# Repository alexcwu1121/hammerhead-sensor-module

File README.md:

# hammerhead-sensor-module

Electrical and software design files for the Hammerhead Sensor Module, top level control system of the Hammerhead mobile robot platform.

## 1. Software Development Prerequisites

Development for this project requires working within a devcontainer which has the Hammerhead Sensor Module Yocto SDK installed.

To build the Hammerhead Sensor Module Yocto image and SDK, you should have at least 50Gb of disk space.

For live remote gdb debugging and other niceties, make sure your board runs the development variant of the image, `hammerhead-dev-image`.

1. Note the version of the SDK required by the devcontainer config at `.devcontainer/devcontainer.json`. This is the version of the Hammerhead Yocto manifest which produces the SDK intended to be used with this revision of the Hammerhead Sensor Module software.
2. Pull down the specified tag of the Hammerhead Yocto manifest repo and follow BitBake environment setup instructions: https://github.com/alexcwu1121/yocto-hammerhead
3. Build the core Hammerhead image with SDK. This can take a few hours depending on your build hardware: `bitbake -c populate_sdk hammerhead-core-image`
4. Copy the SDK installer script at `~/build/tmp/deploy/sdk/hammerhead-glibc-x86_64-hammerhead-core-image-cortexa76-hammerhead-toolchain-<version>.sh` to the root of this repo
5. Install Podman >4.x
6. Install VSCode
7. Install VSCode Dev Containers extension
8. In Dev Containers settings, set the following:
    - Docker Path: `podman`
    - Docker Compose Path: `podman-compose`
    - Docker Socket: `/run/podman/podman.sock`
9. Open VSCode to this directory and select from command pallette `Dev Containers: Rebuild and Reopen in Container`
10. VSCode will build the devcontainer, including copying in and installing the SDK. This may take several minutes.

## 2. Deploying and Debugging on Target

The target is expected at `192.168.4.1` (the board's access point gateway), logged in as `root`. Both can be changed in `.vscode/settings.json` (`hammerhead.targetHost`, `hammerhead.targetUser`, `hammerhead.gdbPort`), or with the `HAMMERHEAD_HOST`/`HAMMERHEAD_USER` environment variables when running the scripts directly.

### Target Password

The password is never stored. The first deploy or debug session of a devcontainer session prompts for it in the task terminal, then keeps an SSH master connection open in the background; later deploys and debug sessions reuse it without prompting. The connection closes when the devcontainer stops or the board drops off the network, after which the next run prompts again. To close it manually (e.g. after reflashing or to switch boards), run `Tasks: Run Task` -> `Target: disconnect`.

### Deploy

From the command palette, `Tasks: Run Task` -> `Deploy: diagnostics`. This builds the `Target-Debug` preset and copies `hsc-diagnostics` to `/opt/diagnostics/` on the target.

Or from a devcontainer terminal:

```
./scripts/deploy.sh build/Target-Debug/cpp/diagnostics/hsc-diagnostics /opt/diagnostics
```

### Remote Debug

From the command palette, `Debug: Select and Start Debugging` -> `Remote Debug: diagnostics` (or `F5`). This builds, deploys, starts `gdbserver` on the target, and attaches the SDK's cross gdb. The application's stdout/stderr appears in the `GDB Server: diagnostics` terminal.

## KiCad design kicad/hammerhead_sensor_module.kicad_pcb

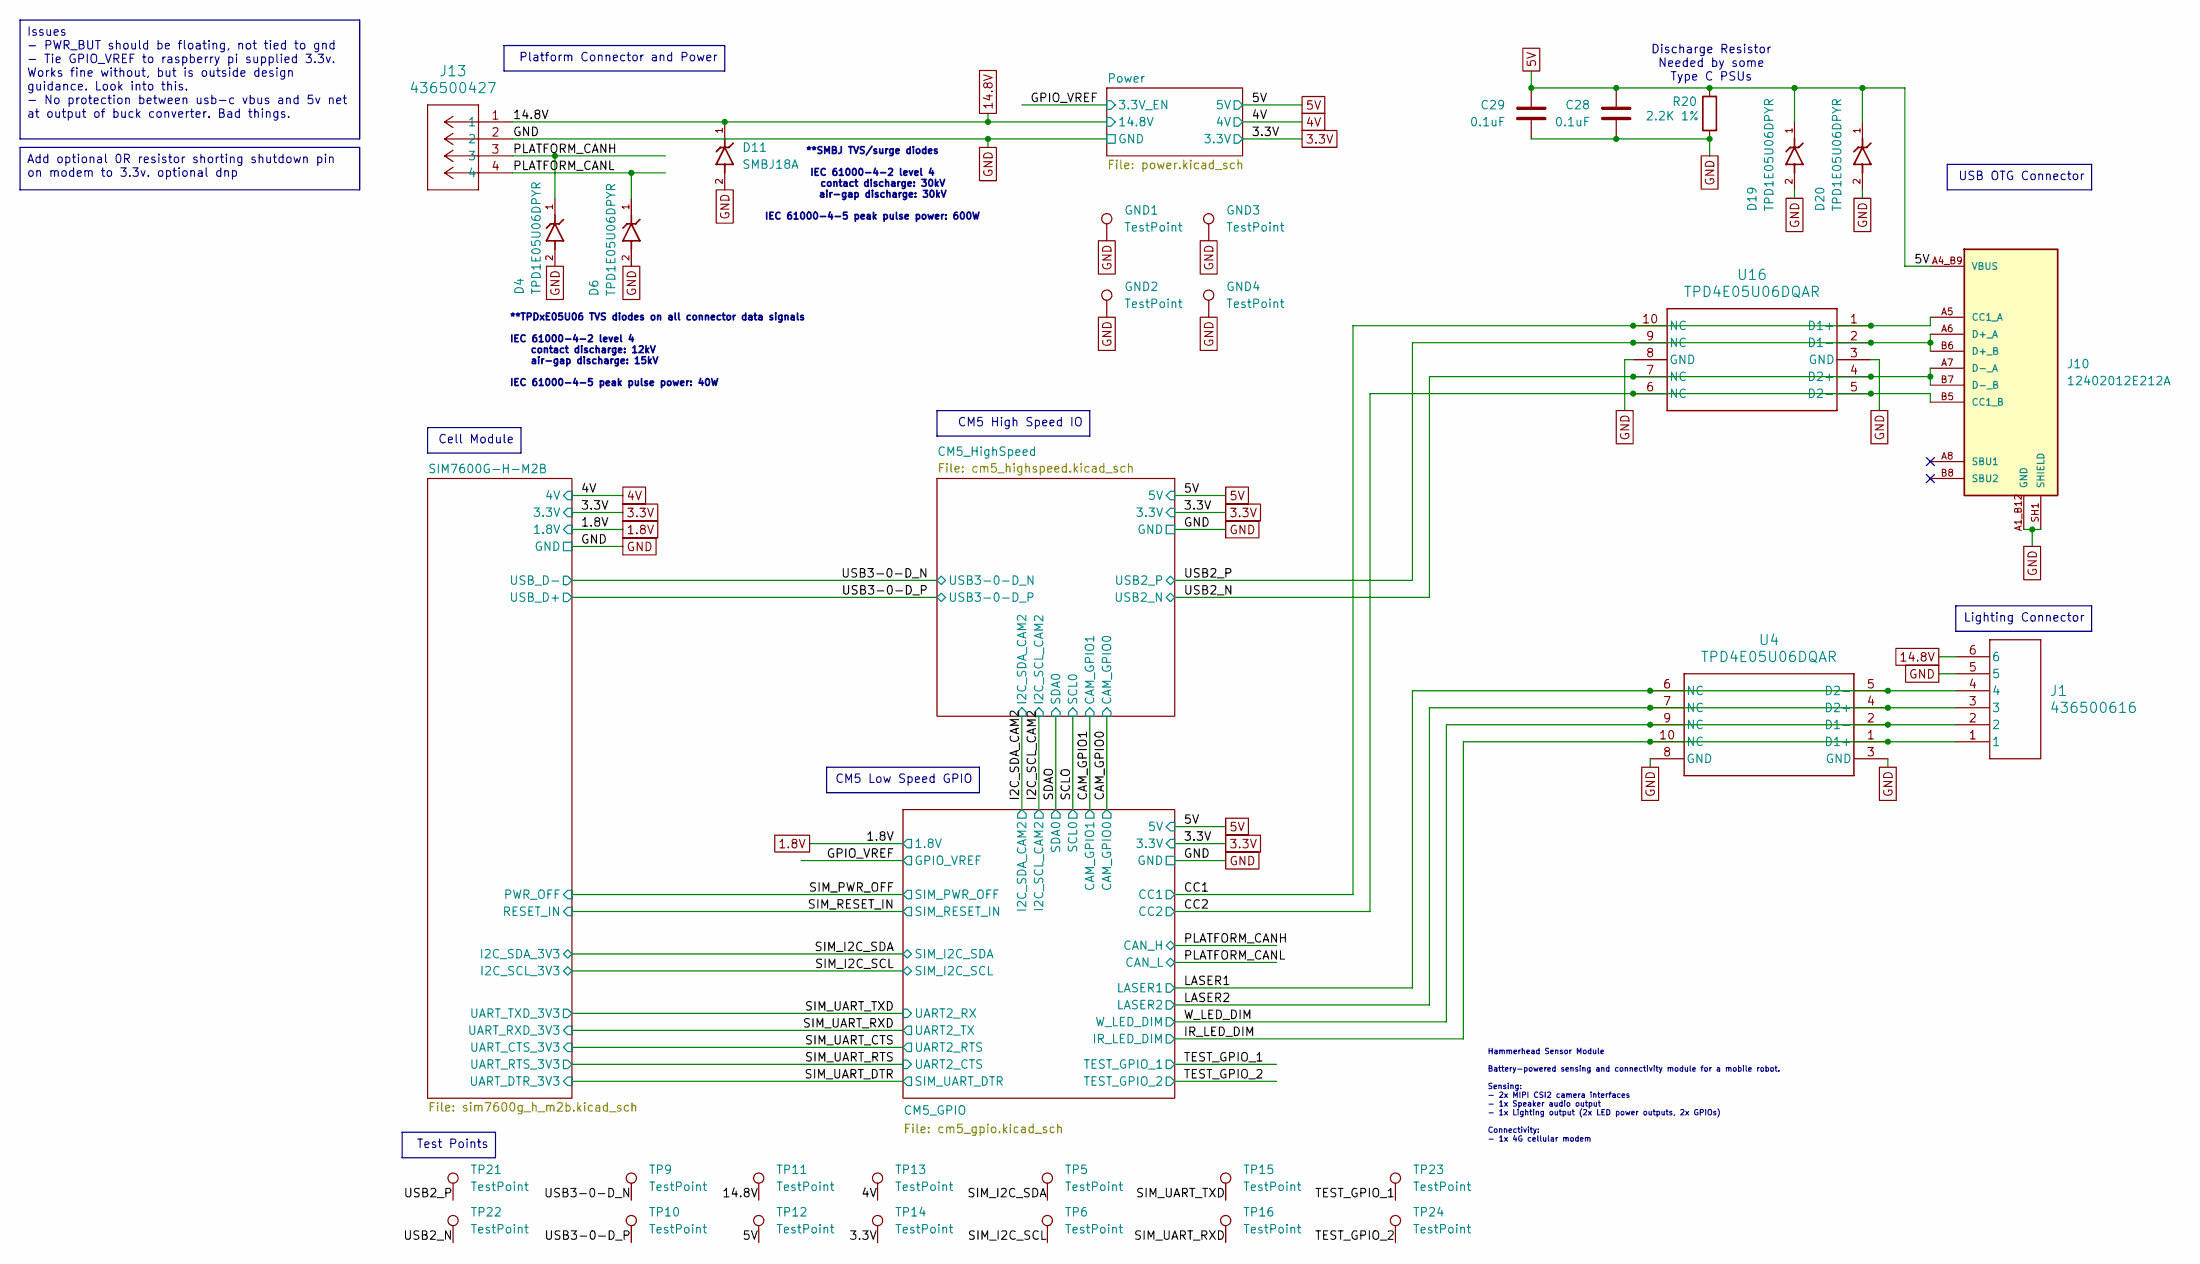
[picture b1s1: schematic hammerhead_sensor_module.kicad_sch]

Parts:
C28, C29: 0.1uF; C_0201_0603Metric
D4, D6, D19, D20: TPD1E05U06DPYR; SON65P60X100X45-2N
D11: SMBJ18A; DIOM5436X261N; PARTREV JC.07/04/25 v4
GND1, GND2, GND3, GND4: TestPoint; TestPoint_Pad_1.0x1.0mm
J1: 436500616; CONN_SD-43650-006_06_MOL
J10: 12402012E212A; AMPHENOL_12402012E212A; PARTREV 4
J13: 436500427; CONN_SD-43650-010_04_MOL
R20: 2.2K 1%; R_0201_0603Metric; Part Description Resistor 2.2K M1005 1% 63mW
TP5, TP6, TP9, TP10, TP11, TP12, TP13, TP14, TP15, TP16, TP21, TP22, TP23, TP24: TestPoint; TestPoint_Pad_1.0x1.0mm
U4, U16: TPD4E05U06DQAR; DQA0010A

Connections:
3.3V: TP14.1; also elsewhere on the board
4V: TP13.1; also elsewhere on the board
5V: C28.1, C29.1, D19.1, D20.1, J10.A4_B9 (VBUS), J10.B4_A9 (VBUS), R20.1, TP12.1; also elsewhere on the board
14.8V: D11.1, J1.6, J13.1, TP11.1; also elsewhere on the board
/CC1: J10.A5 (CC1_A), U16.1 (D1+), U16.10 (NC); also elsewhere on the board
/CC2: J10.B5 (CC1_B), U16.5 (D2-), U16.6 (NC); also elsewhere on the board
/IR_LED_DIM: J1.1, U4.1 (D1+), U4.10 (NC); also elsewhere on the board
/LASER1: J1.4, U4.5 (D2-), U4.6 (NC); also elsewhere on the board
/LASER2: J1.3, U4.4 (D2+), U4.7 (NC); also elsewhere on the board
/PLATFORM_CANH: D4.1, J13.3; also elsewhere on the board
/PLATFORM_CANL: D6.1, J13.4; also elsewhere on the board
/SIM_I2C_SCL: TP6.1; also elsewhere on the board
/SIM_I2C_SDA: TP5.1; also elsewhere on the board
/SIM_UART_RXD: TP16.1; also elsewhere on the board
/SIM_UART_TXD: TP15.1; also elsewhere on the board
/TEST_GPIO_1: TP23.1; also elsewhere on the board
/TEST_GPIO_2: TP24.1; also elsewhere on the board
/USB2_N: J10.A7 (D-_A), J10.B7 (D-_B), TP22.1, U16.4 (D2+), U16.7 (NC); also elsewhere on the board
/USB2_P: J10.A6 (D+_A), J10.B6 (D+_B), TP21.1, U16.2 (D1-), U16.9 (NC); also elsewhere on the board
/USB3-0-D_N: TP9.1; also elsewhere on the board
/USB3-0-D_P: TP10.1; also elsewhere on the board
/W_LED_DIM: J1.2, U4.2 (D1-), U4.9 (NC); also elsewhere on the board
GND: C28.2, C29.2, D4.2, D6.2, D11.2, D19.2, D20.2, GND1.1, GND2.1, GND3.1, GND4.1, J1.5, J10.A1_B12 (GND), J10.B1_A12 (GND), J10.SH1 (SHIELD), J10.SH2 (SHIELD), J10.SH3 (SHIELD), J10.SH4 (SHIELD), J13.2, R20.2, U4.3 (GND), U4.8 (GND), U16.3 (GND), U16.8 (GND); also elsewhere on the board

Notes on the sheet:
Hammerhead Sensor Module Battery-powered sensing and connectivity module for a mobile robot. Sensing: - 2x MIPI CSI2 camera interfaces - 1x Speaker audio output - 1x Lighting output (2x LED power outputs, 2x GPIOs) Connectivity: - 1x 4G cellular modem
**SMBJ TVS/surge diodes IEC 61000-4-2 level 4 contact discharge: 30kV air-gap discharge: 30kV IEC 61000-4-5 peak pulse power: 600W
**TPDxE05U06 TVS diodes on all connector data signals IEC 61000-4-2 level 4 contact discharge: 12kV air-gap discharge: 15kV IEC 61000-4-5 peak pulse power: 40W
Discharge Resistor Needed by some Type C PSUs
Cell Module
Test Points
Issues - PWR_BUT should be floating, not tied to gnd - Tie GPIO_VREF to raspberry pi supplied 3.3v. Works fine without, but is outside design guidance. Look into this. - No protection between usb-c vbus and 5v net at output of buck converter. Bad things.
Add optional 0R resistor shorting shutdown pin on modem to 3.3v. optional dnp
USB OTG Connector
CM5 High Speed IO
Platform Connector and Power
Lighting Connector
CM5 Low Speed GPIO

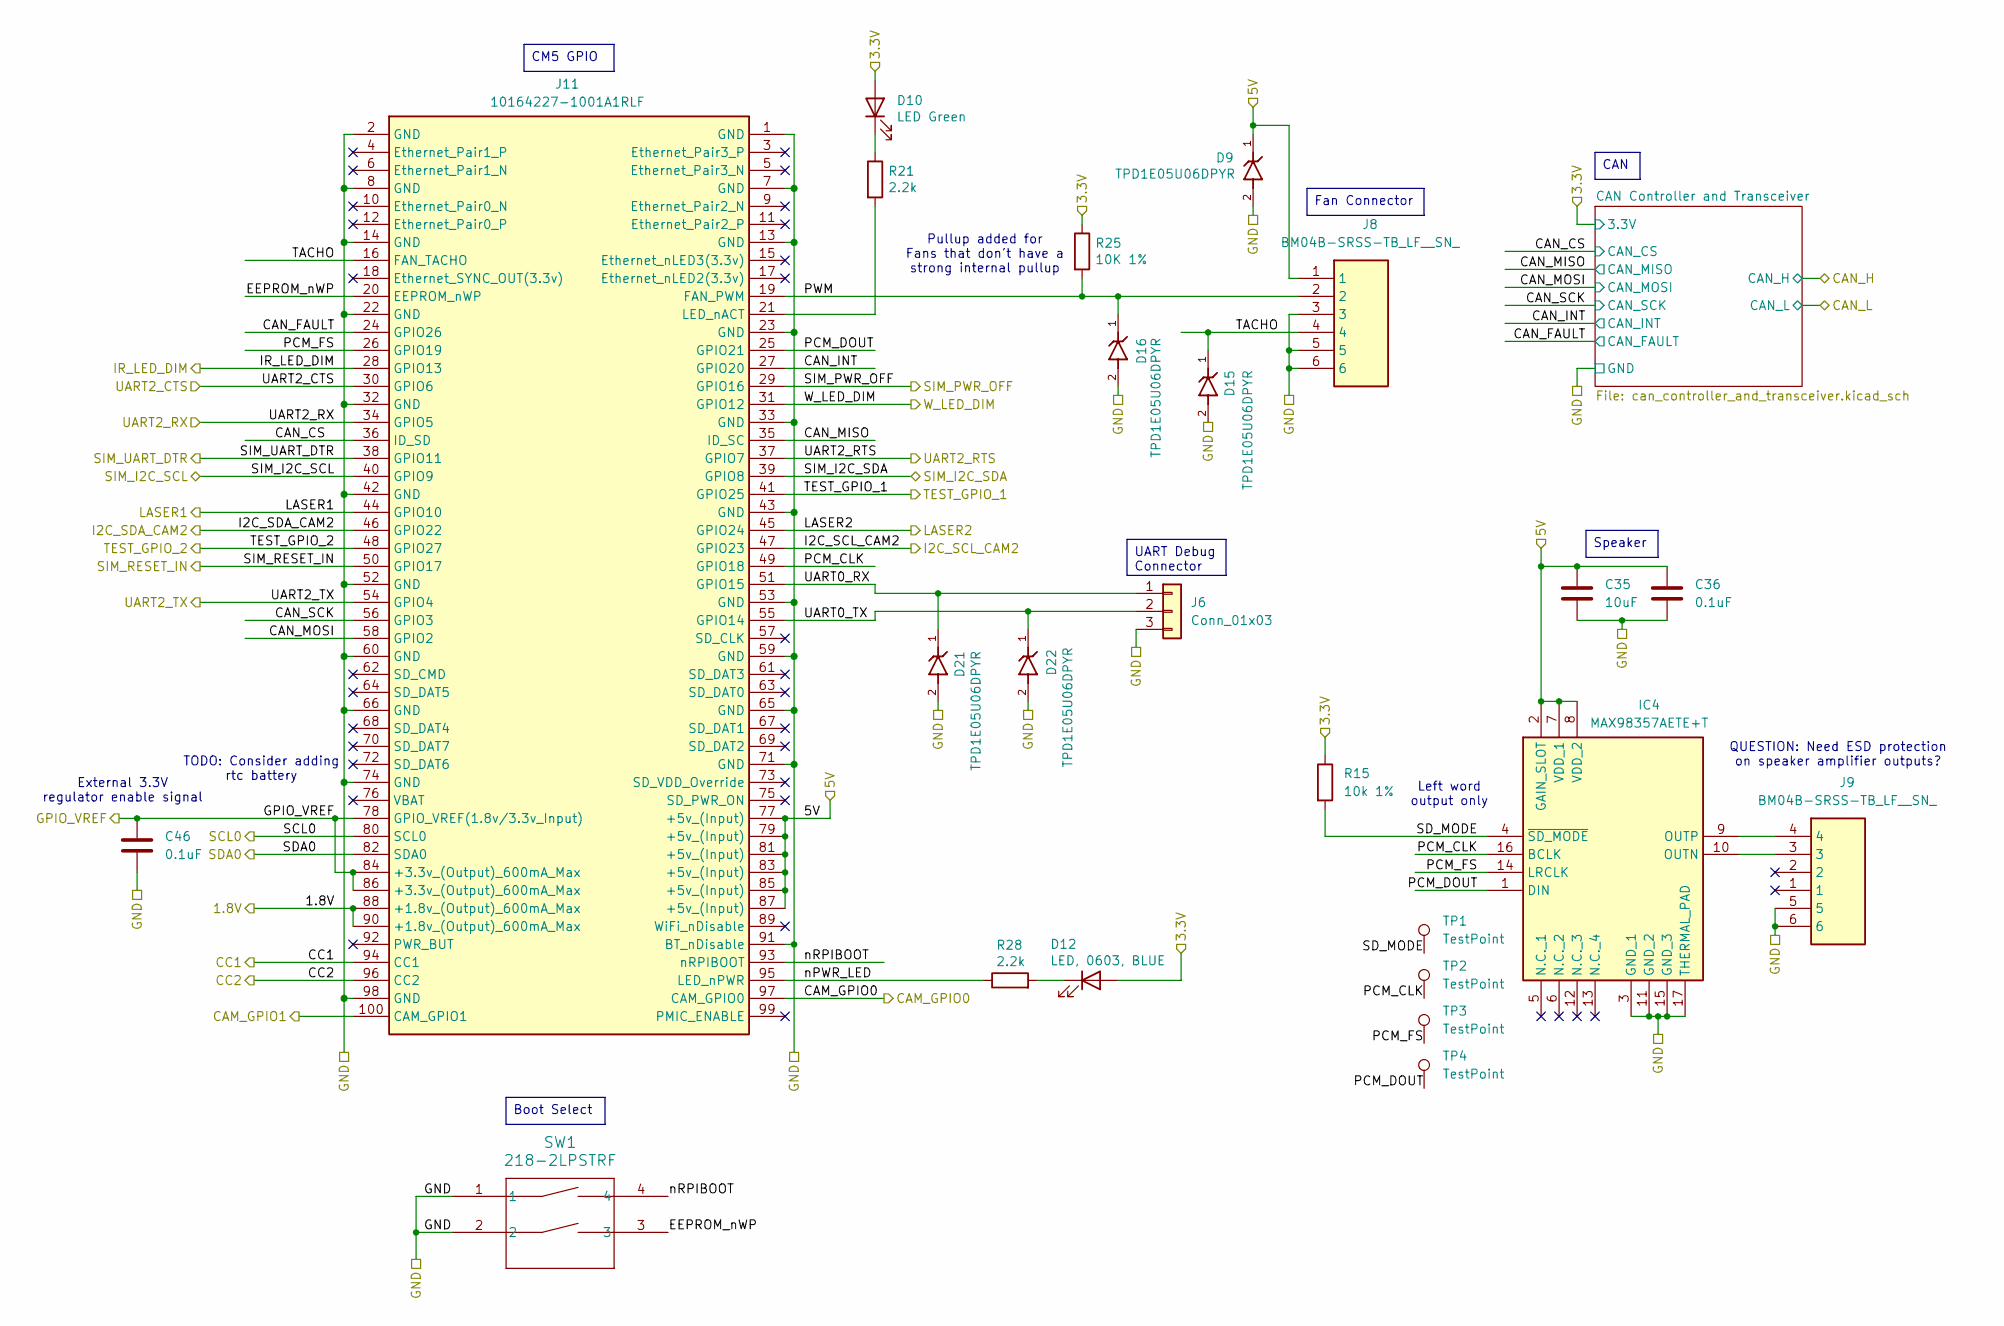
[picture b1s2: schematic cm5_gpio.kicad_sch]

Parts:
C35: 10uF; C_0603_1608Metric
C36, C46: 0.1uF; C_0201_0603Metric
D9, D15, D16, D21, D22: TPD1E05U06DPYR; SON65P60X100X45-2N
D10: LED Green; LED_0603_1608Metric; Part Description Green 572nm LED Indication - Discrete 2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
D12: LED, 0603, BLUE; LED_0603_1608Metric; Part Description Red 620nm LED Indication - Discrete 2.2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
IC4: MAX98357AETE+T; QFN50P300X300X80-17N; Manufacturer_Part_Number MAX98357AETE+T; Mouser Part Number 700-MAX98357AETE+T
J6: Conn_01x03; PinHeader_1x03_P2.54mm_Vertical
J8, J9: BM04B-SRSS-TB_LF__SN_; BM04B-SRSS-TB_LFSN_; Manufacturer_Part_Number BM04B-SRSS-TB(LF)(SN); Mouser Part Number N/A
J11: 10164227-1001A1RLF; 101642271001A1RLF; Manufacturer_Part_Number 10164227-1001A1RLF; Mouser Part Number 649-01642271001A1RLF
R15: 10k 1%; R_0201_0603Metric
R21, R28: 2.2k; R_0201_0603Metric; Part Description Resistor 1K M1005 1% 63mW
R25: 10K 1%; R_0201_0603Metric; Part Description Resistor 10K M1005 1% 63mW
SW1: 218-2LPSTRF; 218-2-GULLWING_CTS
TP1, TP2, TP3, TP4: TestPoint; TestPoint_Pad_1.0x1.0mm

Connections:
1.8V: J11.88 (+1.8v_(Output)_600mA_Max), J11.90 (+1.8v_(Output)_600mA_Max); also elsewhere on the board
3.3V: D10.2 (A), D12.2 (A), R15.1, R25.1; also elsewhere on the board
5V: C35.1, C36.1, D9.1, IC4.2 (GAIN_SLOT), IC4.7 (VDD_1), IC4.8 (VDD_2), J8.1, J11.77 (+5v_(Input)), J11.79 (+5v_(Input)), J11.81 (+5v_(Input)), J11.83 (+5v_(Input)), J11.85 (+5v_(Input)), J11.87 (+5v_(Input)); also elsewhere on the board
/CAM_GPIO0: J11.97 (CAM_GPIO0); also elsewhere on the board
/CAM_GPIO1: J11.100 (CAM_GPIO1); also elsewhere on the board
/CC1: J11.94 (CC1); also elsewhere on the board
/CC2: J11.96 (CC2); also elsewhere on the board
/CM5_GPIO/CAN_CS: J11.36 (ID_SD); also elsewhere on the board
/CM5_GPIO/CAN_FAULT: J11.24 (GPIO26); also elsewhere on the board
/CM5_GPIO/CAN_INT: J11.27 (GPIO20); also elsewhere on the board
/CM5_GPIO/CAN_MISO: J11.35 (ID_SC); also elsewhere on the board
/CM5_GPIO/CAN_MOSI: J11.58 (GPIO2); also elsewhere on the board
/CM5_GPIO/CAN_SCK: J11.56 (GPIO3); also elsewhere on the board
/CM5_GPIO/EEPROM_nWP: J11.20 (EEPROM_nWP), SW1.3
/CM5_GPIO/PCM_CLK: IC4.16 (BCLK), J11.49 (GPIO18), TP2.1
/CM5_GPIO/PCM_DOUT: IC4.1 (DIN), J11.25 (GPIO21), TP4.1
/CM5_GPIO/PCM_FS: IC4.14 (LRCLK), J11.26 (GPIO19), TP3.1
/CM5_GPIO/PWM: D16.1, J8.2, J11.19 (FAN_PWM), R25.2
/CM5_GPIO/SD_MODE: IC4.4 (~SD_MODE), R15.2, TP1.1
/CM5_GPIO/TACHO: D15.1, J8.4, J11.16 (FAN_TACHO)
/CM5_GPIO/UART0_RX: D21.1, J6.1, J11.51 (GPIO15)
/CM5_GPIO/UART0_TX: D22.1, J6.2, J11.55 (GPIO14)
/CM5_GPIO/nPWR_LED: J11.95 (LED_nPWR), R28.1
/CM5_GPIO/nRPIBOOT: J11.93 (nRPIBOOT), SW1.4
/GPIO_VREF: C46.1, J11.78 (GPIO_VREF(1.8v/3.3v_Input)), J11.84 (+3.3v_(Output)_600mA_Max), J11.86 (+3.3v_(Output)_600mA_Max); also elsewhere on the board
/I2C_SCL_CAM2: J11.47 (GPIO23); also elsewhere on the board
/I2C_SDA_CAM2: J11.46 (GPIO22); also elsewhere on the board
/IR_LED_DIM: J11.28 (GPIO13); also elsewhere on the board
/LASER1: J11.44 (GPIO10); also elsewhere on the board
/LASER2: J11.45 (GPIO24); also elsewhere on the board
/SCLO: J11.80 (SCL0); also elsewhere on the board
/SDAO: J11.82 (SDA0); also elsewhere on the board
/SIM_I2C_SCL: J11.40 (GPIO9); also elsewhere on the board
/SIM_I2C_SDA: J11.39 (GPIO8); also elsewhere on the board
/SIM_PWR_OFF: J11.29 (GPIO16); also elsewhere on the board
/SIM_RESET_IN: J11.50 (GPIO17); also elsewhere on the board
/SIM_UART_CTS: J11.37 (GPIO7); also elsewhere on the board
/SIM_UART_DTR: J11.38 (GPIO11); also elsewhere on the board
/SIM_UART_RTS: J11.30 (GPIO6); also elsewhere on the board
/SIM_UART_RXD: J11.54 (GPIO4); also elsewhere on the board
/SIM_UART_TXD: J11.34 (GPIO5); also elsewhere on the board
/TEST_GPIO_1: J11.41 (GPIO25); also elsewhere on the board
/TEST_GPIO_2: J11.48 (GPIO27); also elsewhere on the board
/W_LED_DIM: J11.31 (GPIO12); also elsewhere on the board
GND: C35.2, C36.2, C46.2, D9.2, D15.2, D16.2, D21.2, D22.2, IC4.3 (GND_1), IC4.11 (GND_2), IC4.15 (GND_3), IC4.17 (THERMAL_PAD), J6.3, J8.3, J8.5, J8.6, J9.5, J9.6, J11.1 (GND), J11.2 (GND), J11.7 (GND), J11.8 (GND), J11.13 (GND), J11.14 (GND), J11.22 (GND), J11.23 (GND), J11.32 (GND), J11.33 (GND), J11.42 (GND), J11.43 (GND), J11.52 (GND), J11.53 (GND), J11.59 (GND), J11.60 (GND), J11.65 (GND), J11.66 (GND), J11.71 (GND), J11.74 (GND), J11.91 (BT_nDisable), J11.98 (GND), SW1.1, SW1.2; also elsewhere on the board
unnamed: D10.1 (K), R21.1
unnamed: D12.1 (K), R28.2
unnamed: IC4.10 (OUTN), J9.3
unnamed: IC4.9 (OUTP), J9.4
unnamed: J11.21 (LED_nACT), R21.2

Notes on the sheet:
External 3.3V regulator enable signal
TODO: Consider adding rtc battery
Pullup added for Fans that don't have a strong internal pullup
QUESTION: Need ESD protection on speaker amplifier outputs?
Left word output only
UART Debug Connector
CM5 GPIO
Speaker
Boot Select
Fan Connector
CAN

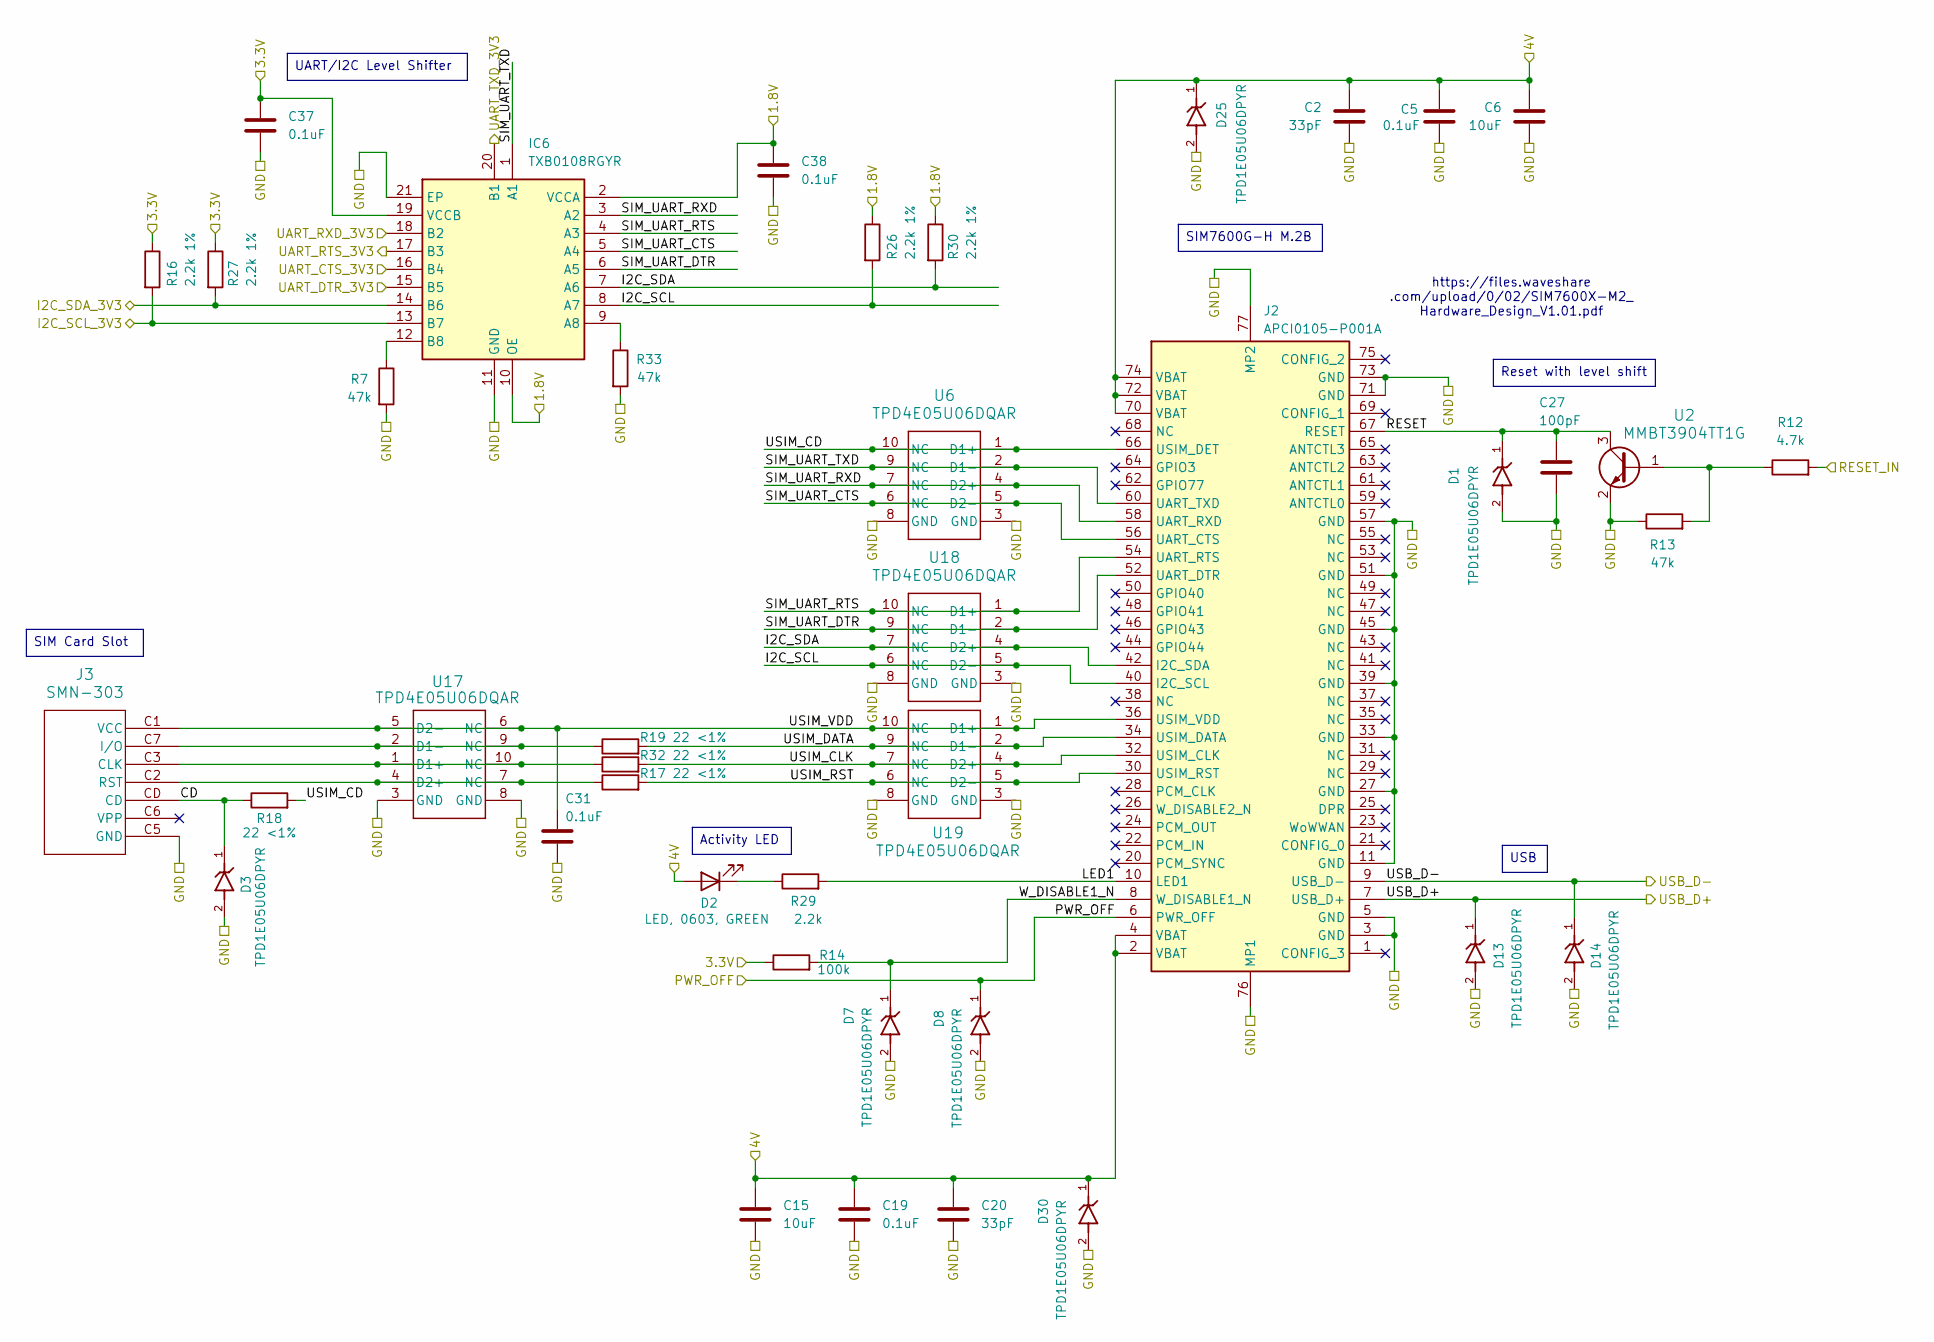
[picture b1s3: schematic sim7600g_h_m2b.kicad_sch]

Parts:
C2, C20: 33pF; C_0402_1005Metric
C5, C19: 0.1uF; C_0402_1005Metric
C6, C15: 10uF; C_0603_1608Metric
C27: 100pF; C_0201_0603Metric
C31, C37, C38: 0.1uF; C_0201_0603Metric
D1, D3, D7, D8, D13, D14, D25, D30: TPD1E05U06DPYR; SON65P60X100X45-2N
D2: LED, 0603, GREEN; D_0603_1608Metric
IC6: TXB0108RGYR; SN74LVC541ARGYR; Manufacturer_Part_Number TXB0108RGYR; Mouser Part Number 595-TXB0108RGYR
J2: APCI0105-P001A; APCI0105P001A; Manufacturer_Part_Number APCI0105-P001A
J3: SMN-303; SMN-303_XNP
R7, R13, R33: 47k; R_0201_0603Metric
R12: 4.7k; R_0201_0603Metric
R14: 100k; R_0201_0603Metric
R16, R26, R27, R30: 2.2k 1%; R_0201_0603Metric
R17, R18, R19, R32: 22 <1%; R_0201_0603Metric
R29: 2.2k; R_0201_0603Metric
U2: MMBT3904TT1G; SOT-416_1P65X0P9_ONS-L
U6, U17, U18, U19: TPD4E05U06DQAR; DQA0010A

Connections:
1.8V: C38.1, IC6.2 (VCCA), IC6.10 (OE), R26.1, R30.1; also elsewhere on the board
3.3V: C37.1, IC6.19 (VCCB), R14.1, R16.1, R27.1; also elsewhere on the board
4V: C2.1, C5.1, C6.1, C15.1, C19.1, C20.1, D2.2 (A), D25.1, D30.1, J2.2 (VBAT), J2.4 (VBAT), J2.70 (VBAT), J2.72 (VBAT), J2.74 (VBAT); also elsewhere on the board
/SIM7600G-H-M2B/CD: D3.1, J3.CD, R18.1
/SIM7600G-H-M2B/I2C_SCL: IC6.8 (A7), J2.40 (I2C_SCL), R26.2, U18.5 (D2-), U18.6 (NC)
/SIM7600G-H-M2B/I2C_SDA: IC6.7 (A6), J2.42 (I2C_SDA), R30.2, U18.4 (D2+), U18.7 (NC)
/SIM7600G-H-M2B/LED1: J2.10 (LED1), R29.2
/SIM7600G-H-M2B/RESET: C27.1, D1.1, J2.67 (RESET), U2.3
/SIM7600G-H-M2B/SIM_UART_CTS: IC6.5 (A4), J2.56 (UART_CTS), U6.5 (D2-), U6.6 (NC)
/SIM7600G-H-M2B/SIM_UART_DTR: IC6.6 (A5), J2.52 (UART_DTR), U18.2 (D1-), U18.9 (NC)
/SIM7600G-H-M2B/SIM_UART_RTS: IC6.4 (A3), J2.54 (UART_RTS), U18.1 (D1+), U18.10 (NC)
/SIM7600G-H-M2B/SIM_UART_RXD: IC6.3 (A2), J2.58 (UART_RXD), U6.4 (D2+), U6.7 (NC)
/SIM7600G-H-M2B/SIM_UART_TXD: IC6.1 (A1), J2.60 (UART_TXD), U6.2 (D1-), U6.9 (NC)
/SIM7600G-H-M2B/USIM_CD: J2.66 (USIM_DET), R18.2, U6.1 (D1+), U6.10 (NC)
/SIM7600G-H-M2B/USIM_CLK: J2.32 (USIM_CLK), R32.2, U19.4 (D2+), U19.7 (NC)
/SIM7600G-H-M2B/USIM_DATA: J2.34 (USIM_DATA), R19.2, U19.2 (D1-), U19.9 (NC)
/SIM7600G-H-M2B/USIM_RST: J2.30 (USIM_RST), R17.2, U19.5 (D2-), U19.6 (NC)
/SIM7600G-H-M2B/USIM_VDD: C31.1, J2.36 (USIM_VDD), J3.C1 (VCC), U17.5 (D2-), U17.6 (NC), U19.1 (D1+), U19.10 (NC)
/SIM7600G-H-M2B/W_DISABLE1_N: D7.1, J2.8 (W_DISABLE1_N), R14.2
/SIM_I2C_SCL: IC6.13 (B7), R16.2; also elsewhere on the board
/SIM_I2C_SDA: IC6.14 (B6), R27.2; also elsewhere on the board
/SIM_PWR_OFF: D8.1, J2.6 (PWR_OFF); also elsewhere on the board
/SIM_RESET_IN: R12.2; also elsewhere on the board
/SIM_UART_CTS: IC6.16 (B4); also elsewhere on the board
/SIM_UART_DTR: IC6.15 (B5); also elsewhere on the board
/SIM_UART_RTS: IC6.17 (B3); also elsewhere on the board
/SIM_UART_RXD: IC6.18 (B2); also elsewhere on the board
/SIM_UART_TXD: IC6.20 (B1); also elsewhere on the board
/USB3-0-D_N: D14.1, J2.9 (USB_D-); also elsewhere on the board
/USB3-0-D_P: D13.1, J2.7 (USB_D+); also elsewhere on the board
GND: C2.2, C5.2, C6.2, C15.2, C19.2, C20.2, C27.2, C31.2, C37.2, C38.2, D1.2, D3.2, D7.2, D8.2, D13.2, D14.2, D25.2, D30.2, IC6.11 (GND), IC6.21 (EP), J2.3 (GND), J2.5 (GND), J2.11 (GND), J2.27 (GND), J2.33 (GND), J2.39 (GND), J2.45 (GND), J2.51 (GND), J2.57 (GND), J2.71 (GND), J2.73 (GND), J2.76 (MP1), J2.77 (MP2), J3.C5 (GND), R7.2, R13.1, R33.2, U2.2, U6.3 (GND), U6.8 (GND), U17.3 (GND), U17.8 (GND), U18.3 (GND), U18.8 (GND), U19.3 (GND), U19.8 (GND); also elsewhere on the board
unnamed: D2.1 (K), R29.1
unnamed: IC6.9 (A8), R33.1
unnamed: IC6.12 (B8), R7.1
unnamed: J3.C3 (CLK), R32.1, U17.1 (D1+), U17.10 (NC)
unnamed: J3.C7 (I/O), R19.1, U17.2 (D1-), U17.9 (NC)
unnamed: J3.C2 (RST), R17.1, U17.4 (D2+), U17.7 (NC)
unnamed: R12.1, R13.2, U2.1

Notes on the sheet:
https://files.waveshare .com/upload/0/02/SIM7600X-M2_ Hardware_Design_V1.01.pdf
USB
Reset with level shift
SIM Card Slot
SIM7600G-H M.2B
Activity LED
UART/I2C Level Shifter

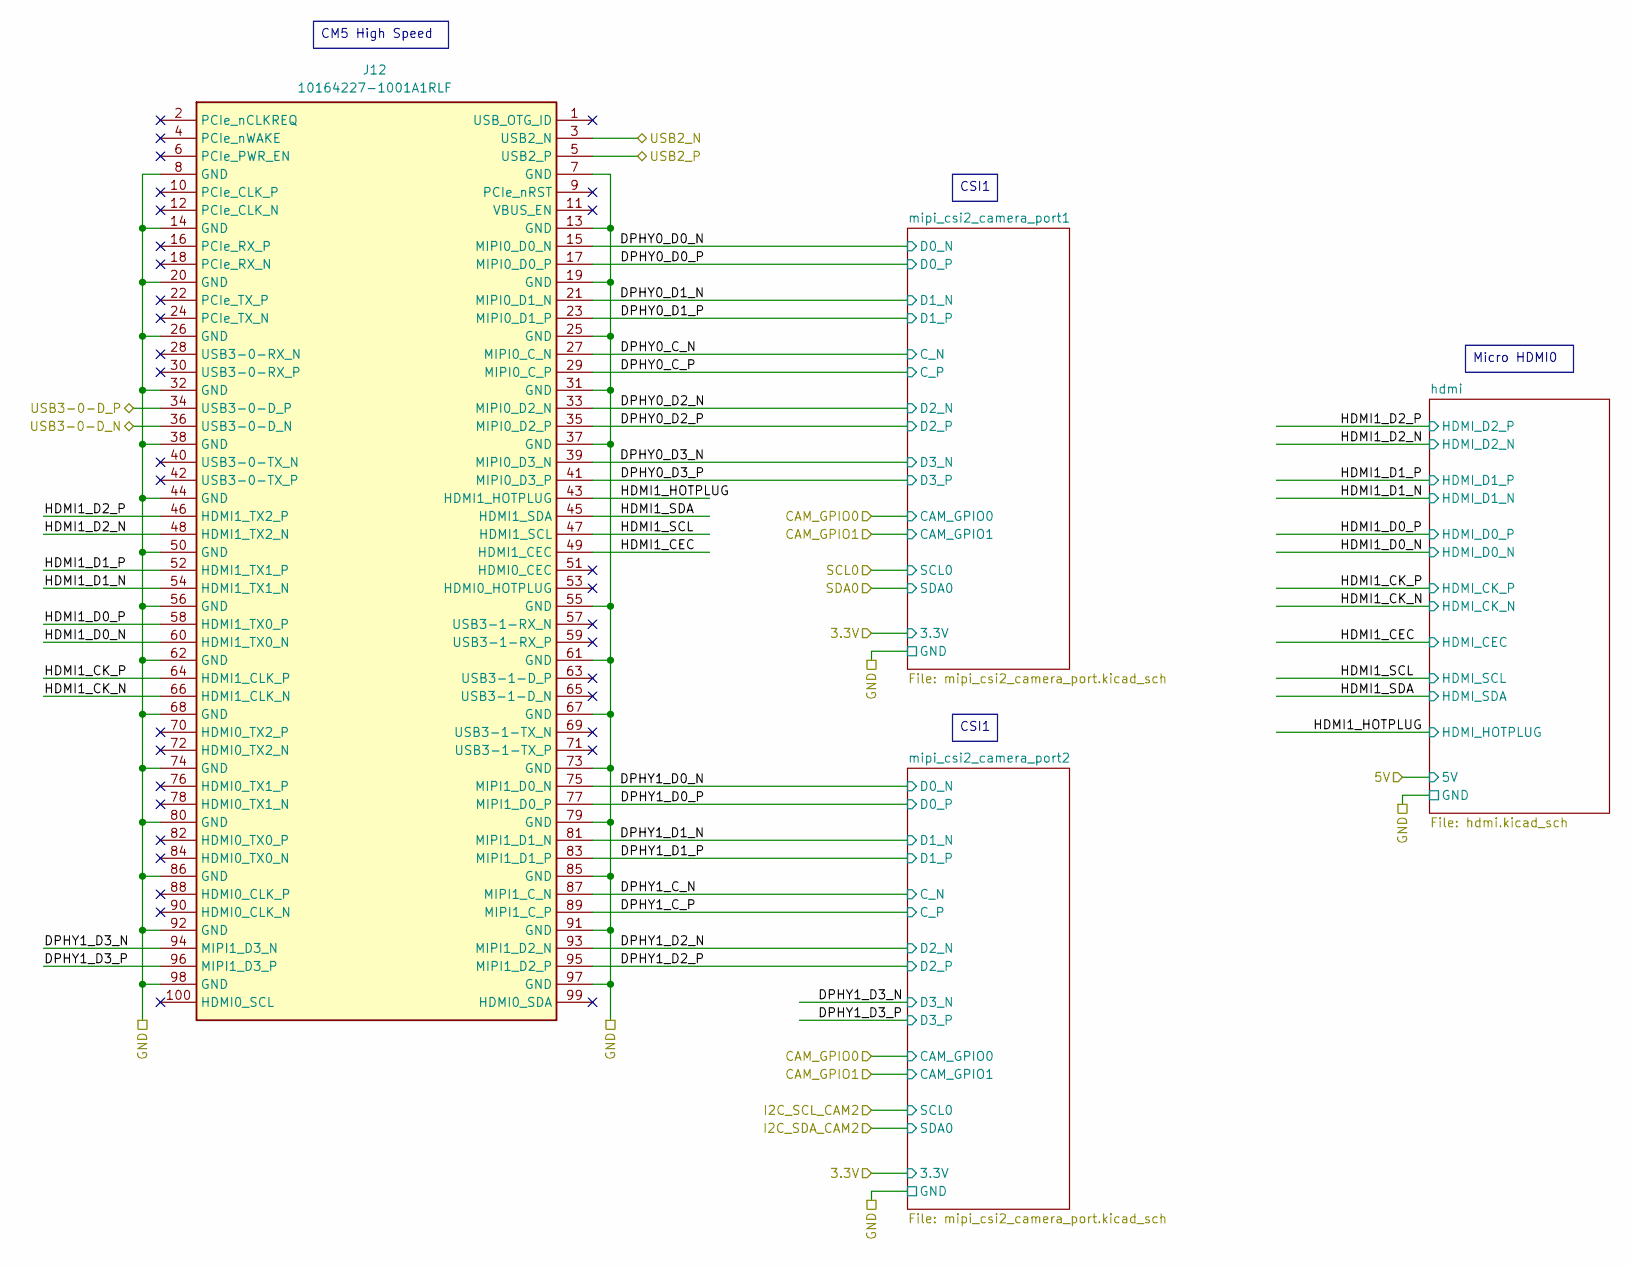
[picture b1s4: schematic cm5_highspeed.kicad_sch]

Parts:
J12: 10164227-1001A1RLF; 101642271001A1RLF; Manufacturer_Part_Number 10164227-1001A1RLF; Mouser Part Number 649-01642271001A1RLF

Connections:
/CM5_HighSpeed/DPHY0_C_N: J12.27 (MIPI0_C_N); also elsewhere on the board
/CM5_HighSpeed/DPHY0_C_P: J12.29 (MIPI0_C_P); also elsewhere on the board
/CM5_HighSpeed/DPHY0_D0_N: J12.15 (MIPI0_D0_N); also elsewhere on the board
/CM5_HighSpeed/DPHY0_D0_P: J12.17 (MIPI0_D0_P); also elsewhere on the board
/CM5_HighSpeed/DPHY0_D1_N: J12.21 (MIPI0_D1_N); also elsewhere on the board
/CM5_HighSpeed/DPHY0_D1_P: J12.23 (MIPI0_D1_P); also elsewhere on the board
/CM5_HighSpeed/DPHY0_D2_N: J12.33 (MIPI0_D2_N); also elsewhere on the board
/CM5_HighSpeed/DPHY0_D2_P: J12.35 (MIPI0_D2_P); also elsewhere on the board
/CM5_HighSpeed/DPHY0_D3_N: J12.39 (MIPI0_D3_N); also elsewhere on the board
/CM5_HighSpeed/DPHY0_D3_P: J12.41 (MIPI0_D3_P); also elsewhere on the board
/CM5_HighSpeed/DPHY1_C_N: J12.87 (MIPI1_C_N); also elsewhere on the board
/CM5_HighSpeed/DPHY1_C_P: J12.89 (MIPI1_C_P); also elsewhere on the board
/CM5_HighSpeed/DPHY1_D0_N: J12.75 (MIPI1_D0_N); also elsewhere on the board
/CM5_HighSpeed/DPHY1_D0_P: J12.77 (MIPI1_D0_P); also elsewhere on the board
/CM5_HighSpeed/DPHY1_D1_N: J12.81 (MIPI1_D1_N); also elsewhere on the board
/CM5_HighSpeed/DPHY1_D1_P: J12.83 (MIPI1_D1_P); also elsewhere on the board
/CM5_HighSpeed/DPHY1_D2_N: J12.93 (MIPI1_D2_N); also elsewhere on the board
/CM5_HighSpeed/DPHY1_D2_P: J12.95 (MIPI1_D2_P); also elsewhere on the board
/CM5_HighSpeed/DPHY1_D3_N: J12.94 (MIPI1_D3_N); also elsewhere on the board
/CM5_HighSpeed/DPHY1_D3_P: J12.96 (MIPI1_D3_P); also elsewhere on the board
/CM5_HighSpeed/HDMI1_CEC: J12.49 (HDMI1_CEC); also elsewhere on the board
/CM5_HighSpeed/HDMI1_CK_N: J12.66 (HDMI1_CLK_N); also elsewhere on the board
/CM5_HighSpeed/HDMI1_CK_P: J12.64 (HDMI1_CLK_P); also elsewhere on the board
/CM5_HighSpeed/HDMI1_D0_N: J12.60 (HDMI1_TX0_N); also elsewhere on the board
/CM5_HighSpeed/HDMI1_D0_P: J12.58 (HDMI1_TX0_P); also elsewhere on the board
/CM5_HighSpeed/HDMI1_D1_N: J12.54 (HDMI1_TX1_N); also elsewhere on the board
/CM5_HighSpeed/HDMI1_D1_P: J12.52 (HDMI1_TX1_P); also elsewhere on the board
/CM5_HighSpeed/HDMI1_D2_N: J12.48 (HDMI1_TX2_N); also elsewhere on the board
/CM5_HighSpeed/HDMI1_D2_P: J12.46 (HDMI1_TX2_P); also elsewhere on the board
/CM5_HighSpeed/HDMI1_HOTPLUG: J12.43 (HDMI1_HOTPLUG); also elsewhere on the board
/CM5_HighSpeed/HDMI1_SCL: J12.47 (HDMI1_SCL); also elsewhere on the board
/CM5_HighSpeed/HDMI1_SDA: J12.45 (HDMI1_SDA); also elsewhere on the board
/USB2_N: J12.3 (USB2_N); also elsewhere on the board
/USB2_P: J12.5 (USB2_P); also elsewhere on the board
/USB3-0-D_N: J12.36 (USB3-0-D_N); also elsewhere on the board
/USB3-0-D_P: J12.34 (USB3-0-D_P); also elsewhere on the board
GND: J12.7 (GND), J12.8 (GND), J12.13 (GND), J12.14 (GND), J12.19 (GND), J12.20 (GND), J12.25 (GND), J12.26 (GND), J12.31 (GND), J12.32 (GND), J12.37 (GND), J12.38 (GND), J12.44 (GND), J12.50 (GND), J12.55 (GND), J12.56 (GND), J12.61 (GND), J12.62 (GND), J12.67 (GND), J12.68 (GND), J12.73 (GND), J12.74 (GND), J12.79 (GND), J12.80 (GND), J12.85 (GND), J12.86 (GND), J12.91 (GND), J12.92 (GND), J12.97 (GND), J12.98 (GND); also elsewhere on the board

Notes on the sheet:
CSI1
Micro HDMI0
CM5 High Speed
